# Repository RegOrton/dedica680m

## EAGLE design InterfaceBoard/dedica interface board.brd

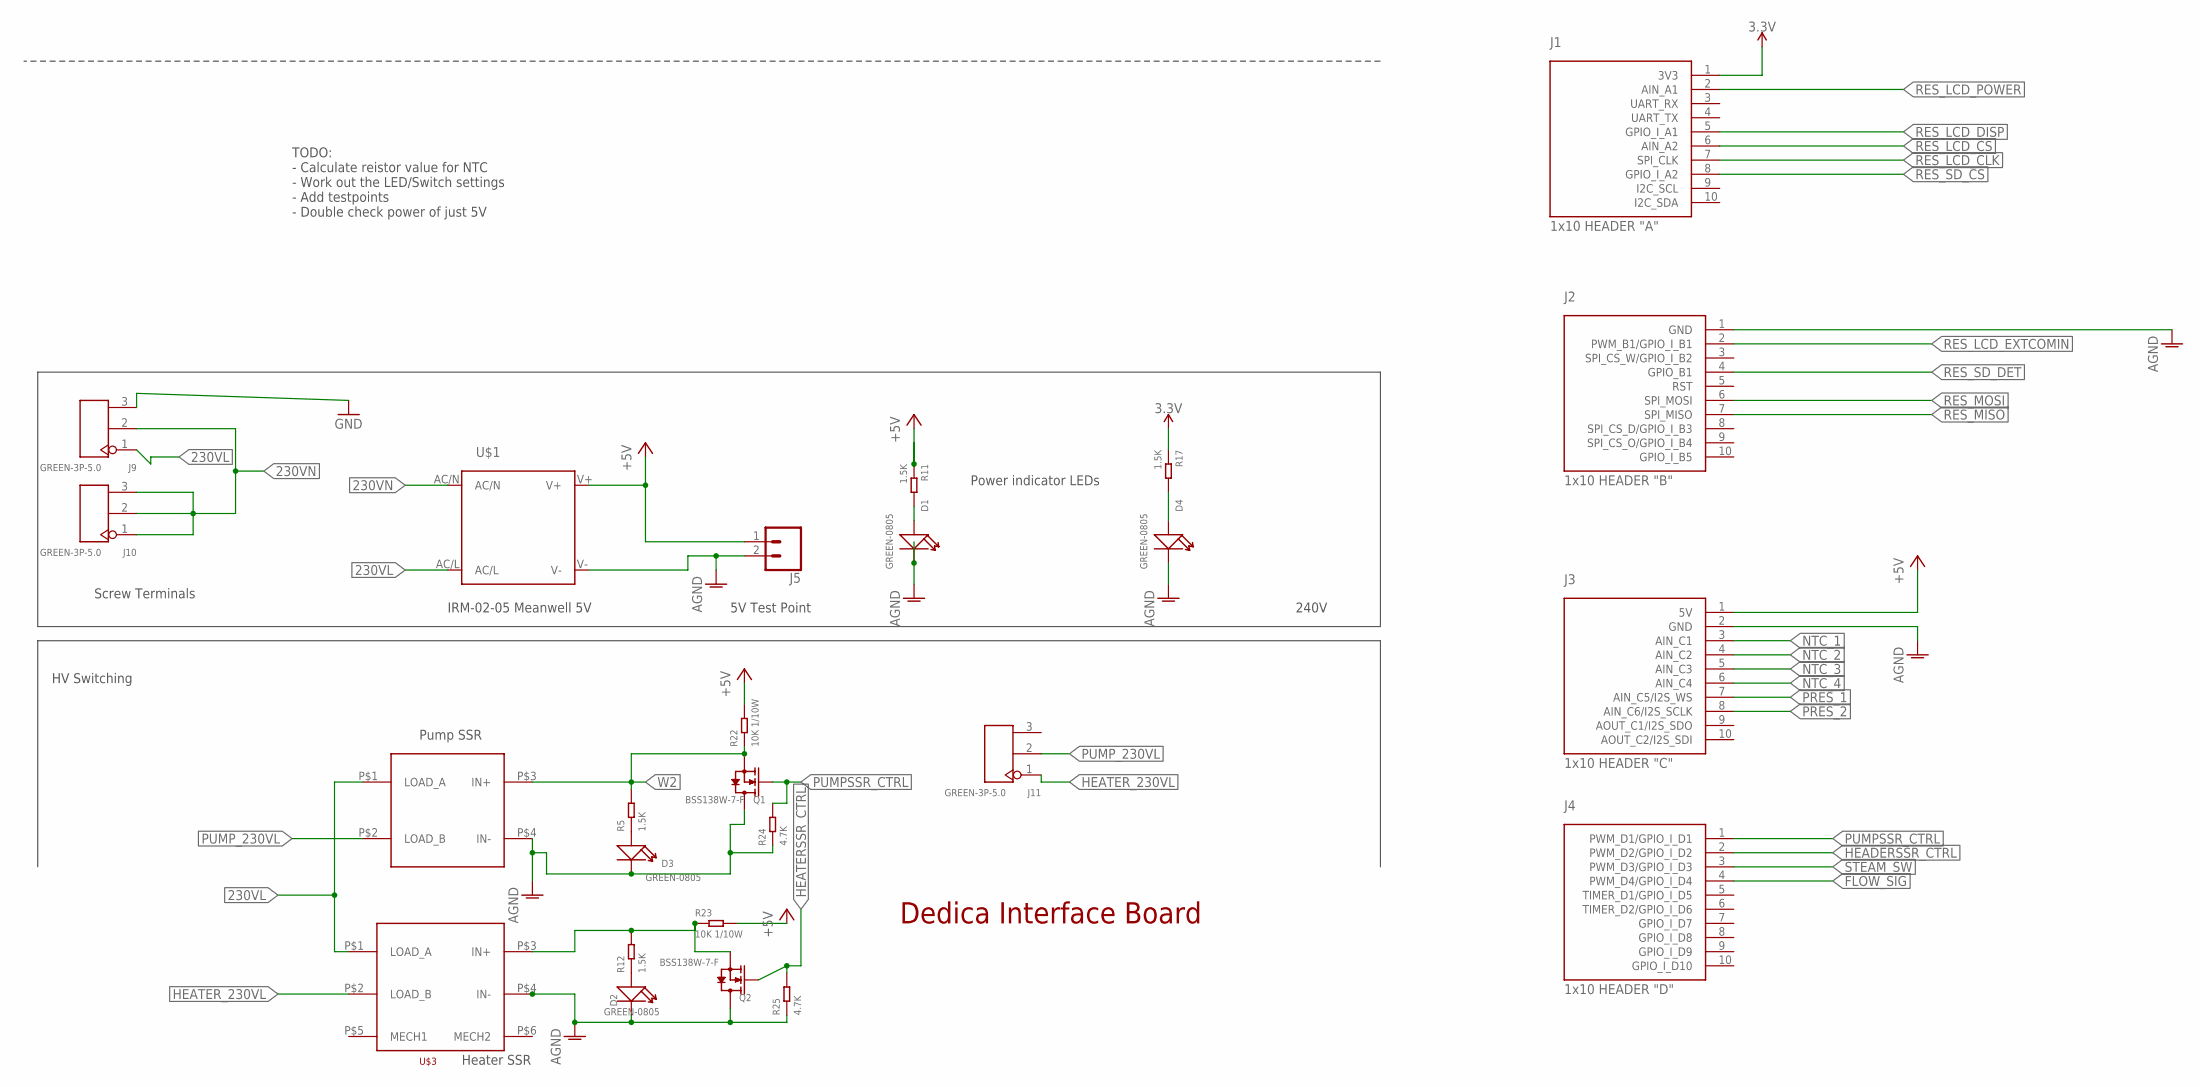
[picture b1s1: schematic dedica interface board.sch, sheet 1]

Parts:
D1, D2, D3, D4: GREEN-0805; LED-0805
J1: 1x10 HEADER "A"; 1X10
J2: 1x10 HEADER "B"; 1X10
J3: 1x10 HEADER "C"; 1X10
J4: 1x10 HEADER "D"; 1X10
J5: CONN_02; 1X02
J9, J10, J11: GREEN-3P-5.0; H3-5.0-15.5X8.0MM
Q1, Q2: BSS138W-7-F; SOT-23
R5, R11, R12, R17: 1.5K; R0603
R22, R23: 10K 1/10W; R0603
R24, R25: 4.7K; R0603
U$1: IRM_01/02IRM_01/02; IRM_01/02
U$2: AQ3A2-ZT4/32VDC
U$3: AQ10A2-ZT4/32VDC

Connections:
3.3V: J1.1 (3V3), R17.1; also elsewhere on the board
230VL: J9.1, U$1.AC/L, U$2.P$1 (LOAD_A), U$3.P$1 (LOAD_A)
230VN: J9.2, J10.1, J10.2, J10.3, U$1.AC/N
+5V: J3.1 (5V), J5.1, R11.1, R22.2, R23.2, U$1.V+; also elsewhere on the board
AGND: D1.-, D2.-, D3.-, D4.-, J2.1 (GND), J3.2 (GND), J5.2, Q1.3 (D), Q2.3 (D), R24.1, R25.1, U$1.V-, U$2.P$4 (IN-), U$3.P$4 (IN-); also elsewhere on the board
FLOW_SIG: J4.4 (PWM_D4/GPIO_I_D4); also elsewhere on the board
GND: J9.3
HEADERSSR_CTRL: J4.2 (PWM_D2/GPIO_I_D2)
HEATERSSR_CTRL: Q2.1 (G), R25.2
HEATER_230VL: J11.1, U$3.P$2 (LOAD_B)
unnamed: D1.+, R11.2
unnamed: D3.+, R5.1
unnamed: D2.+, R12.1
unnamed: D4.+, R17.2
unnamed: Q2.2 (S), R12.2, R23.1, U$3.P$3 (IN+)
NTC_1: J3.3 (AIN_C1); also elsewhere on the board
NTC_2: J3.4 (AIN_C2); also elsewhere on the board
NTC_3: J3.5 (AIN_C3); also elsewhere on the board
NTC_4: J3.6 (AIN_C4); also elsewhere on the board
PRES_1: J3.7 (AIN_C5/I2S_WS); also elsewhere on the board
PRES_2: J3.8 (AIN_C6/I2S_SCLK); also elsewhere on the board
PUMPSSR_CTRL: J4.1 (PWM_D1/GPIO_I_D1), Q1.1 (G), R24.2
PUMP_230VL: J11.2, U$2.P$2 (LOAD_B)
RES_LCD_CLK: J1.7 (SPI_CLK)
RES_LCD_CS: J1.6 (AIN_A2)
RES_LCD_DISP: J1.5 (GPIO_I_A1)
RES_LCD_EXTCOMIN: J2.2 (PWM_B1/GPIO_I_B1)
RES_LCD_POWER: J1.2 (AIN_A1)
RES_MISO: J2.7 (SPI_MISO)
RES_MOSI: J2.6 (SPI_MOSI)
RES_SD_CS: J1.8 (GPIO_I_A2)
RES_SD_DET: J2.4 (GPIO_B1)
STEAM_SW: J4.3 (PWM_D3/GPIO_I_D3); also elsewhere on the board
W2: Q1.2 (S), R5.2, R22.1, U$2.P$3 (IN+)

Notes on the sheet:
Dedica Interface Board
240V
Screw Terminals
Heater SSR
Pump SSR
HV Switching
IRM-02-05 Meanwell 5V
5V Test Point
Power indicator LEDs
TODO: - Calculate reistor value for NTC - Work out the LED/Switch settings - Add testpoints - Double check power of just 5V

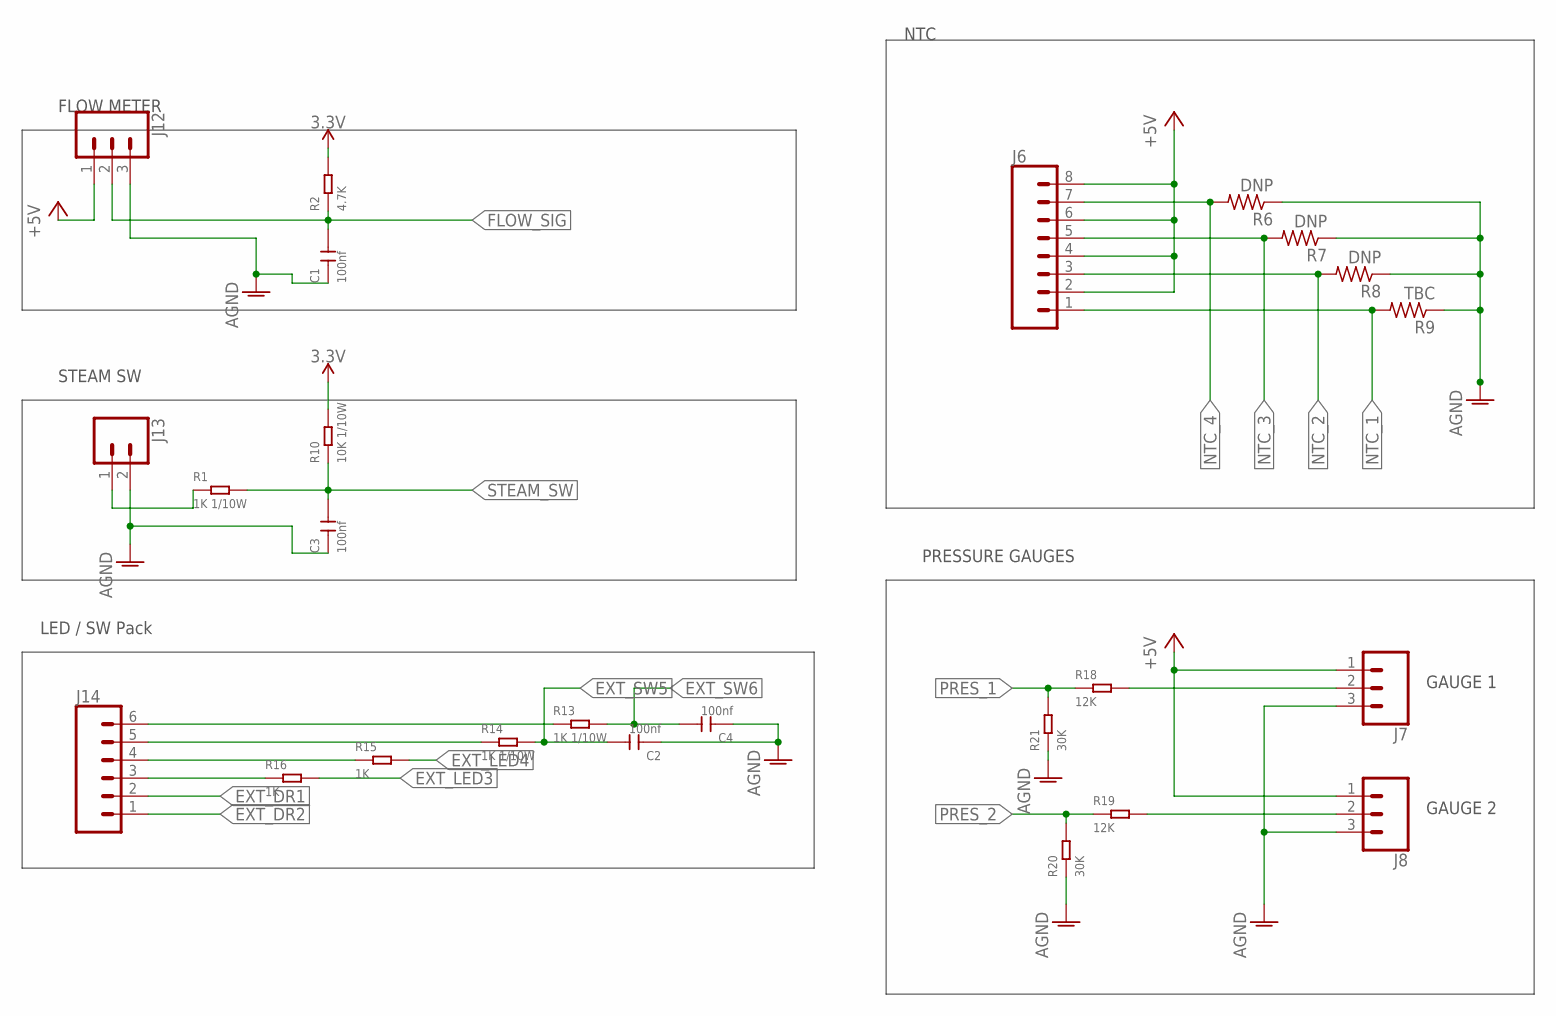
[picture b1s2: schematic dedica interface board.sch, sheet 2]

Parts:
C1, C2, C3, C4: 100nf; C0603
J6: CONN_08"; 1X08
J7, J8, J12: CONN_03; 1X03
J13: CONN_02; 1X02
J14: CONN_06LOCK; 1X06_LOCK
R1, R13, R14: 1K 1/10W; R0603
R2: 4.7K; R0603
R6, R7, R8: DNP; R0603
R9: TBC; R0603
R10: 10K 1/10W; R0603
R15, R16: 1K; R0805
R18, R19: 12K; R0603
R20, R21: 30K; R0603

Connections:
3.3V: R2.2, R10.2; also elsewhere on the board
+5V: J6.2, J6.4, J6.6, J6.8, J7.1, J8.1, J12.1; also elsewhere on the board
AGND: C1.1, C2.1, C3.1, C4.1, J7.3, J8.3, J12.3, J13.2, R6.1, R7.1, R8.1, R9.1, R20.1, R21.1; also elsewhere on the board
EXT_DR1: J14.2
EXT_DR2: J14.1
EXT_LED3: R16.2
EXT_LED4: R15.2
EXT_SW5: C2.2, R14.2
EXT_SW6: C4.2, R13.2
FLOW_SIG: C1.2, J12.2, R2.1; also elsewhere on the board
unnamed: J13.1, R1.1
unnamed: J14.6, R13.1
unnamed: J14.5, R14.1
unnamed: J14.4, R15.1
unnamed: J14.3, R16.1
NTC_1: J6.1, R9.2; also elsewhere on the board
NTC_2: J6.3, R8.2; also elsewhere on the board
NTC_3: J6.5, R7.2; also elsewhere on the board
NTC_4: J6.7, R6.2; also elsewhere on the board
PGAUGE_1: J7.2, R18.2
PGAUGE_2: J8.2, R19.2
PRES_1: R18.1, R21.2; also elsewhere on the board
PRES_2: R19.1, R20.2; also elsewhere on the board
STEAM_SW: C3.2, R1.2, R10.1; also elsewhere on the board

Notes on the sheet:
FLOW METER
STEAM SW
LED / SW Pack
NTC
PRESSURE GAUGES
GAUGE 1
GAUGE 2

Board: 2 copper layers, 50 parts (1 on the bottom side), 32 nets, no tracks yet.

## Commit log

2019-04-04 Hello World Inital Commit
2019-04-04 Basic compile
2019-04-04 LED blink (untested)
2019-04-30 PCB draft 1
2019-04-30 Add SSR and Meanwell Libraries Add SSR and Power Supply to schematic
2019-05-01 3.3V MCU updates

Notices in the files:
parts and their libraries:
SparkFun-Connectors: Licensing: Creative Commons ShareAlike 4.0 International - https://creativecommons.org/licenses/by-sa/4.0
